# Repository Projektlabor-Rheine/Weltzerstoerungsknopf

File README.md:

# Weltzerstoerungsknopf
The Repo of Earth destruction :D

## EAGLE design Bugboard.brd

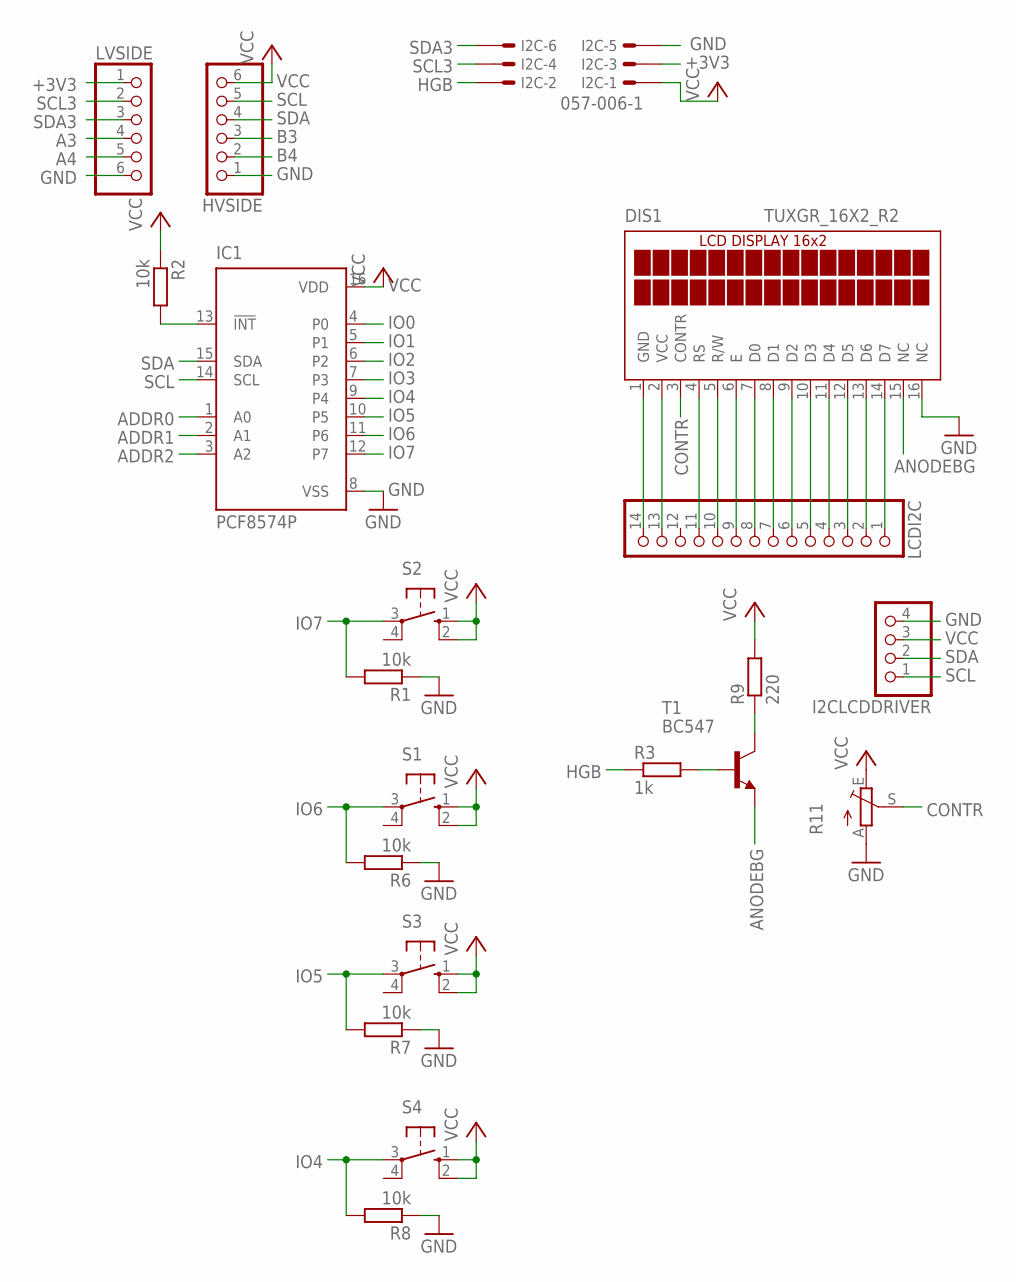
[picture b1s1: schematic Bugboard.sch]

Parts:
DIS1: TUXGR_16X2_R2
HVSIDE: PINHD-1X6; 1X06
I2C: 057-006-1
I2CLCDDRIVER: PINHD-1X4; 1X04
IC1: PCF8574P; DIL16
LCDI2C: PINHD-1X14; 1X14
LVSIDE: PINHD-1X6; 1X06
R1, R2, R6, R7, R8: 10k; 0204/7
R3: 1k; 0207/12
R9: 220; 0204/7
R11: TRIM_EU-B64Y; B64Y
S1, S2, S3, S4: 10-XX; B3F-10XX
T1: BC547; TO92

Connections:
+3V3: I2C.3, LVSIDE.1
A3: LVSIDE.4
A4: LVSIDE.5
ADDR0: IC1.1 (A0)
ADDR1: IC1.2 (A1)
ADDR2: IC1.3 (A2)
ANODEBG: DIS1.15 (NC), T1.1 (E)
B3: HVSIDE.3
B4: HVSIDE.2
CONTR: DIS1.3 (CONTR), R11.S
GND: DIS1.1 (GND), DIS1.16 (NC), HVSIDE.1, I2C.5, I2CLCDDRIVER.4, IC1.8 (VSS), LCDI2C.14, LVSIDE.6, R1.1, R6.1, R7.1, R8.1, R11.A
HGB: I2C.2, R3.1
IO0: IC1.4 (P0)
IO1: IC1.5 (P1)
IO2: IC1.6 (P2)
IO3: IC1.7 (P3)
IO4: IC1.9 (P4), R8.2, S4.3
IO5: IC1.10 (P5), R7.2, S3.3
IO6: IC1.11 (P6), R6.2, S1.3
IO7: IC1.12 (P7), R1.2, S2.3
unnamed: IC1.13 (!INT), R2.2
unnamed: DIS1.14 (D7), LCDI2C.1
unnamed: DIS1.13 (D6), LCDI2C.2
unnamed: DIS1.12 (D5), LCDI2C.3
unnamed: DIS1.11 (D4), LCDI2C.4
unnamed: DIS1.10 (D3), LCDI2C.5
unnamed: DIS1.9 (D2), LCDI2C.6
unnamed: DIS1.8 (D1), LCDI2C.7
unnamed: DIS1.7 (D0), LCDI2C.8
unnamed: DIS1.6 (E), LCDI2C.9
unnamed: DIS1.5 (R/W), LCDI2C.10
unnamed: DIS1.4 (RS), LCDI2C.11
unnamed: R9.1, T1.3 (C)
unnamed: R3.2, T1.2 (B)
SCL: HVSIDE.5, I2CLCDDRIVER.1, IC1.14 (SCL)
SCL3: I2C.4, LVSIDE.2
SDA: HVSIDE.4, I2CLCDDRIVER.2, IC1.15 (SDA)
SDA3: I2C.6, LVSIDE.3
VCC: DIS1.2 (VCC), HVSIDE.6, I2C.1, I2CLCDDRIVER.3, IC1.16 (VDD), LCDI2C.13, R2.1, R9.2, R11.E, S1.1 (S), S1.2 (S1), S2.1 (S), S2.2 (S1), S3.1 (S), S3.2 (S1), S4.1 (S), S4.2 (S1)

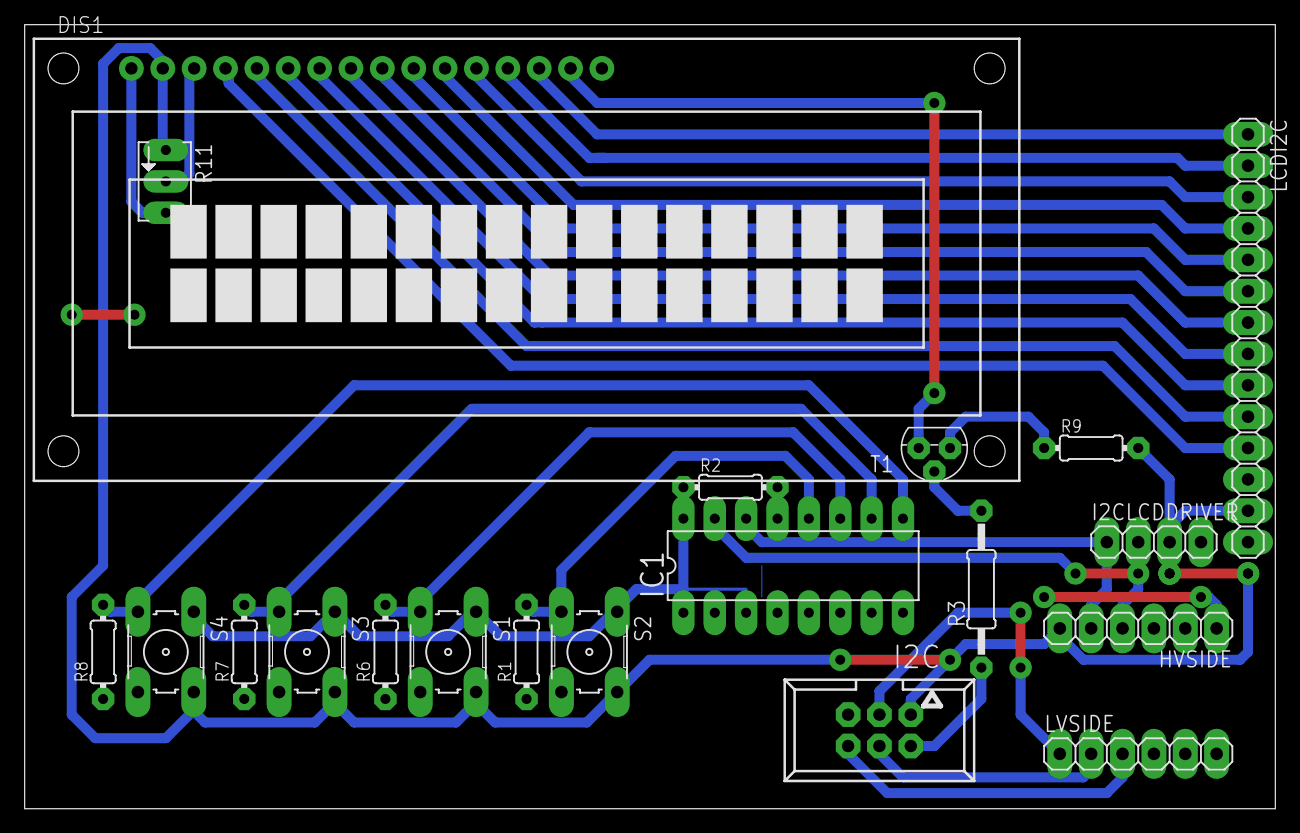
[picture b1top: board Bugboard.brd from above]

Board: 2 copper layers, 101.3 x 63.5 mm, 20 parts (0 on the bottom side), 28 nets.

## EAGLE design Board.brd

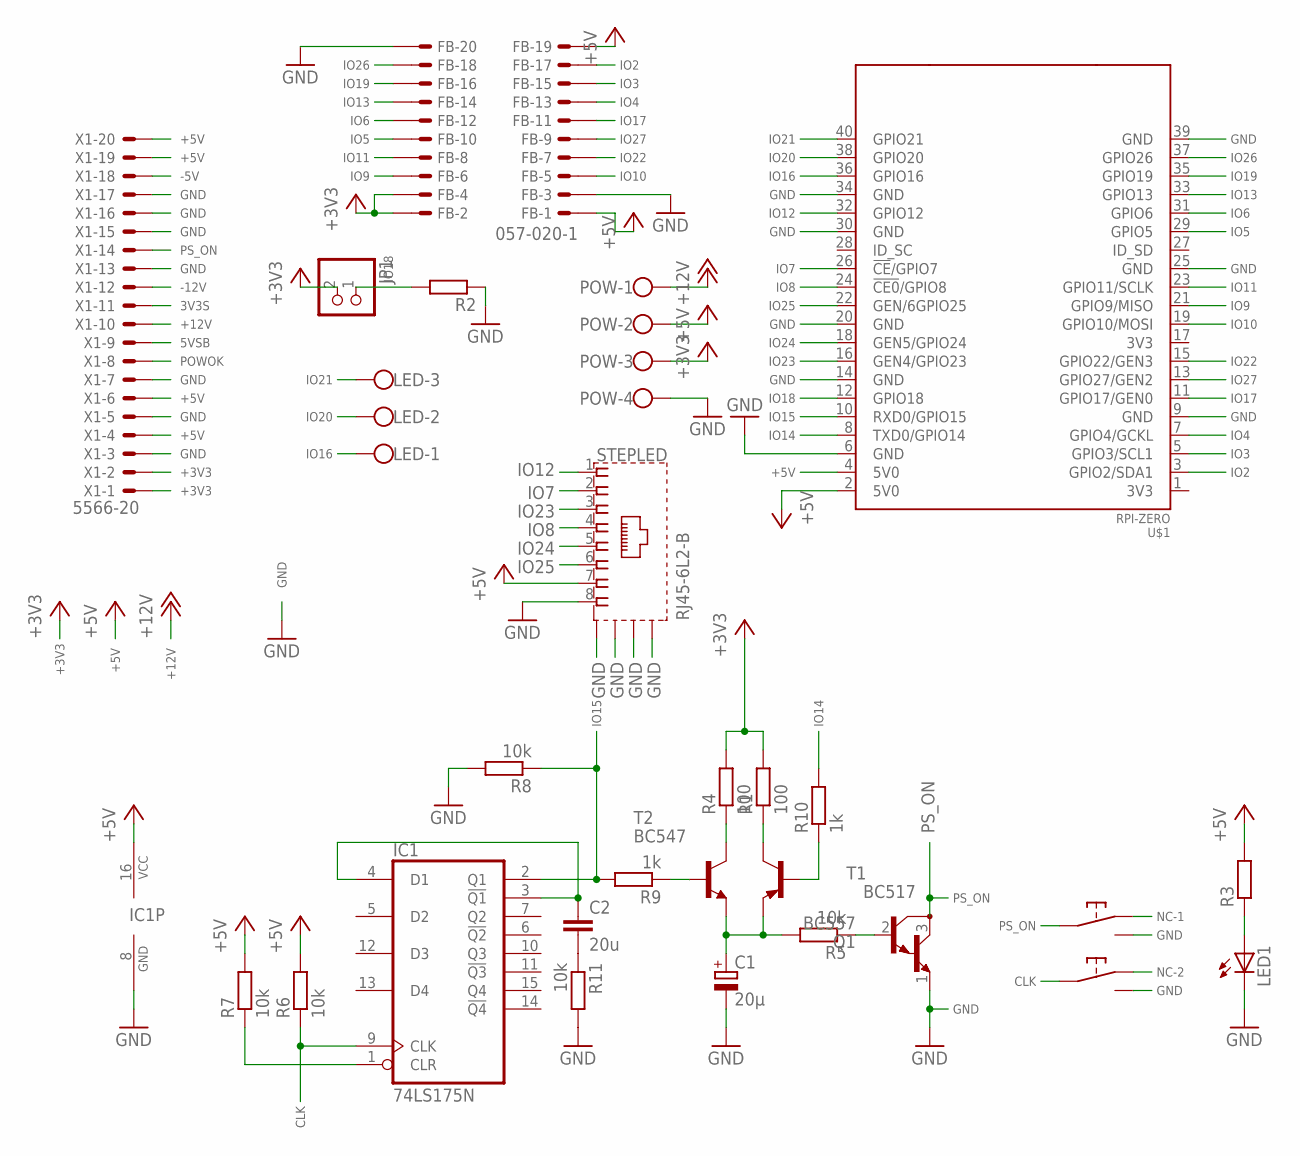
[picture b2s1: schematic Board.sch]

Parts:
C1: 20µ; E2,5-6E
C2: 20u; C050-024X044
FB: 057-020-1
IC1: 74LS175N; DIL16
JP1: PINHD-1X2; 1X02
LED: W237-103
LED1: LED3MM
POW: W237-4
Q1: BC557; TO92
R1, R4: 100; 0204/7
R2: R-EU_0204/7; 0204/7
R3: R-EU_0204/5; 0204/5
R5, R6, R7, R8, R11: 10k; 0204/7
R9, R10: 1k; 0204/7
STEPLED: RJ45-6L2-B; RJ45-SHIELD2
T1: BC517; TO92
T2: BC547; TO92
U$1: RPI-ZERO; RASPBERRYPI_BASTELSTUBE_V13_RASPI_BOARD_B+_FULL
U$2: PC-SWITCH
X1: 5566-20

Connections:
3V3S: X1.11
5VSB: X1.9
+3V3: FB.2, FB.4, JP1.2, POW.3, R1.2, R4.2, X1.1, X1.2
+5V: FB.1, FB.19, IC1.16 (VCC), POW.2, R3.2, R6.2, R7.2, STEPLED.7, U$1.2 (5V0), U$1.4 (5V0), X1.4, X1.6, X1.19, X1.20
+12V: POW.1, X1.10
-5V: X1.18
-12V: X1.12
CLK: IC1.9 (CLK), R6.1, U$2.COM$5
CLR: IC1.1 (CLR), R7.1
GND: C1.-, FB.3, FB.20, IC1.8 (GND), LED1.K (C), POW.4, R2.1, R8.2, R11.2, STEPLED.8, STEPLED.S1 (S), STEPLED.S2 (S), STEPLED.S3 (S), STEPLED.S4 (S), T1.1 (E), U$1.6 (GND), U$1.9 (GND), U$1.14 (GND), U$1.20 (GND), U$1.25 (GND), U$1.30 (GND), U$1.34 (GND), U$1.39 (GND), U$2.NO$3, U$2.NO$6, X1.3, X1.5, X1.7, X1.13, X1.15, X1.16, X1.17
IO2: FB.17, U$1.3 (GPIO2/SDA1)
IO3: FB.15, U$1.5 (GPIO3/SCL1)
IO4: FB.13, U$1.7 (GPIO4/GCKL)
IO5: FB.10, U$1.29 (GPIO5)
IO6: FB.12, U$1.31 (GPIO6)
IO7: STEPLED.2, U$1.26 (!CE!/GPIO7)
IO8: STEPLED.4, U$1.24 (!CE0!/GPIO8)
IO9: FB.6, U$1.21 (GPIO9/MISO)
IO10: FB.5, U$1.19 (GPIO10/MOSI)
IO11: FB.8, U$1.23 (GPIO11/SCLK)
IO12: STEPLED.1, U$1.32 (GPIO12)
IO13: FB.14, U$1.33 (GPIO13)
IO14: R10.2, U$1.8 (TXD0/GPIO14)
IO15: IC1.2 (Q1), R8.1, R9.2, U$1.10 (RXD0/GPIO15)
IO16: LED.1, U$1.36 (GPIO16)
IO17: FB.11, U$1.11 (GPIO17/GEN0)
IO18: JP1.1, R2.2, U$1.12 (GPIO18)
IO19: FB.16, U$1.35 (GPIO19)
IO20: LED.2, U$1.38 (GPIO20)
IO21: LED.3, U$1.40 (GPIO21)
IO22: FB.7, U$1.15 (GPIO22/GEN3)
IO23: STEPLED.3, U$1.16 (GEN4/GPIO23)
IO24: STEPLED.5, U$1.18 (GEN5/GPIO24)
IO25: STEPLED.6, U$1.22 (GEN/6GPIO25)
IO26: FB.18, U$1.37 (GPIO26)
IO27: FB.9, U$1.13 (GPIO27/GEN2)
unnamed: C2.2, R11.1
unnamed: R4.1, T2.3 (C)
unnamed: Q1.3 (C), R1.1
unnamed: Q1.2 (B), R10.1
unnamed: LED1.A, R3.1
unnamed: C2.1, IC1.3 (!Q1), IC1.4 (D1)
unnamed: R9.1, T2.2 (B)
unnamed: R5.1, T1.2 (B)
unnamed: C1.+, Q1.1 (E), R5.2, T2.1 (E)
NC-1: U$2.NC$1
NC-2: U$2.NC$4
POWOK: X1.8
PS_ON: T1.3 (C), U$2.COM$2, X1.14

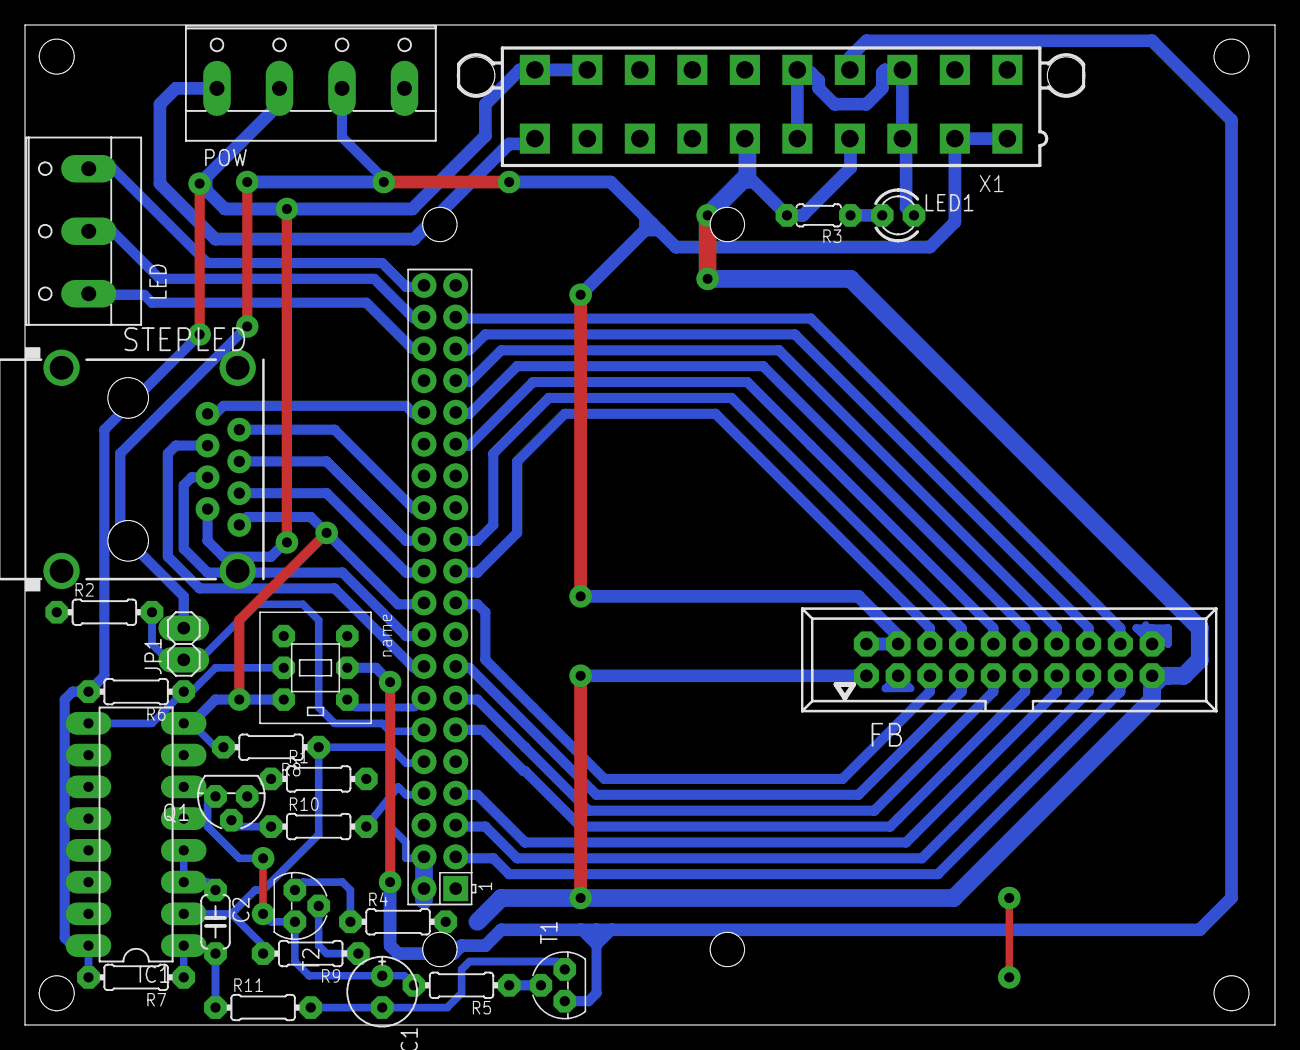
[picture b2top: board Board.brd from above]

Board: 2 copper layers, 100.0 x 80.0 mm, 26 parts (0 on the bottom side), 42 nets.

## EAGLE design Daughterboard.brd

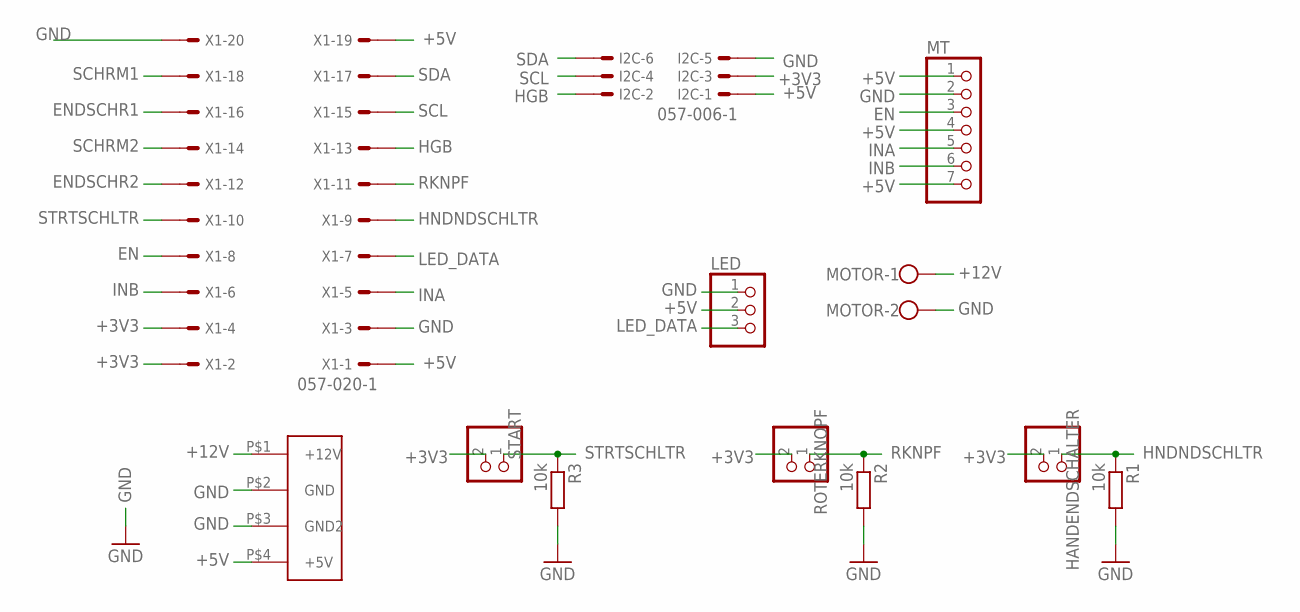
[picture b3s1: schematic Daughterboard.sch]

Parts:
HANDENDSCHALTER: PINHD-1X2; 1X02
I2C: 057-006-1
LED: PINHD-1X3; 1X03
MOTOR: W237-102
MT: PINHD-1X7; 1X07
R1, R2, R3: 10k; 0204/7
ROTERKNOPF: PINHD-1X2; 1X02
START: PINHD-1X2; 1X02
U$1: MOLEX_STECKER; MOLEXCONNECTOR
X1: 057-020-1

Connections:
+3V3: HANDENDSCHALTER.2, I2C.3, ROTERKNOPF.2, START.2, X1.2, X1.4
+5V: I2C.1, LED.2, MT.1, MT.4, MT.7, U$1.P$4 (+5V), X1.1, X1.19
+12V: MOTOR.1, U$1.P$1 (+12V)
EN: MT.3, X1.8
ENDSCHR1: X1.16
ENDSCHR2: X1.12
GND: I2C.5, LED.1, MOTOR.2, MT.2, R1.2, R2.2, R3.2, U$1.P$2 (GND), U$1.P$3 (GND2), X1.3, X1.20
HGB: I2C.2, X1.13
HNDNDSCHLTR: HANDENDSCHALTER.1, R1.1, X1.9
INA: MT.5, X1.5
INB: MT.6, X1.6
LED_DATA: LED.3, X1.7
RKNPF: R2.1, ROTERKNOPF.1, X1.11
SCHRM1: X1.18
SCHRM2: X1.14
SCL: I2C.4, X1.15
SDA: I2C.6, X1.17
STRTSCHLTR: R3.1, START.1, X1.10

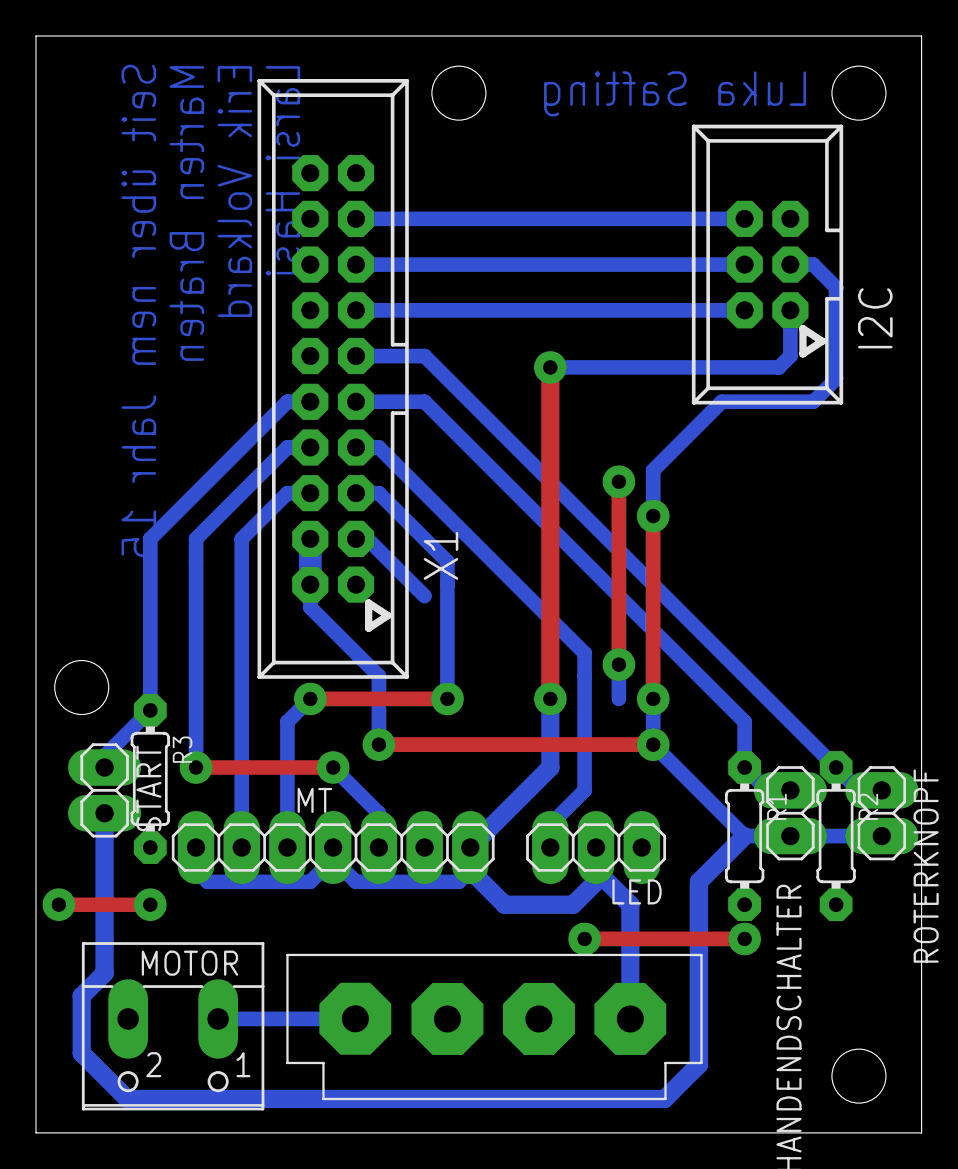
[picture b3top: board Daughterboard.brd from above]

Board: 2 copper layers, 49.2 x 60.9 mm, 12 parts (0 on the bottom side), 14 nets.

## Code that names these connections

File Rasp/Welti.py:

#!/usr/bin/python


#DDDASSSS Selbstzerstörungsskript

import RPi.GPIO as GPIO
import time
import os.path
import os
import asyncio
from functools import partial
from escpos.printer import Usb
import random


#CONST
#Shutdown
#IO14 is already handled
SHTDWN = 15
#schere
SCHM1 = 26
SCHM2 = 13
SCHE1 = 19
SCHE2 = 6
#I2C
SDAP = 2
SCLP = 3
HGB = 4
#Perry
RTKNPF = 17
HNDNDSCHLTR = 27
RTSCHLTR = 5
NEBEL = 16
#Hand
EN = 11
INA = 10
INB = 9
#LED
LEDR = 22
LEDS1 = 21
LEDS2 = 20
#LED Schritte
WLTSCHRFT = 12
STEP1 = 23
STEP2 = 8
STEP3 = 25
#Movement
FORWARD, BACKWARD, STOP = range(0,3)
#Steps
SCHTZKPPSCHLTR, RTNKNPFDRCKN, QUTTNGNTNHMN, OFF = range(4,8)
#otherstuff
counterfile = "/home/pi/Welti/counter.txt"
CRCL = "\n"


#Vars
cntr = 0


#GPIO setup
GPIO.setmode(GPIO.BCM)
GPIO.setwarnings(False)

#Scheren pins
GPIO.setup([SCHM1, SCHM2, NEBEL], GPIO.OUT, initial=GPIO.LOW)
GPIO.setup([SCHE1, SCHE2], GPIO.IN)
#Perry
GPIO.setup([RTKNPF, HNDNDSCHLTR, RTSCHLTR], GPIO.IN)
#Hand
GPIO.setup([EN, INA, INB], GPIO.OUT, initial=GPIO.LOW)
#LED schrift
GPIO.setup([WLTSCHRFT, STEP1, STEP2, STEP3], GPIO.OUT, initial=GPIO.HIGH)
#Shutdown
GPIO.setup(SHTDWN, GPIO.IN)

#Event detect
GPIO.add_event_detect(SHTDWN, GPIO.FALLING)

#Printer setupo
p = Usb(0x0416, 0x5011)

#Startup IO
if not(os.path.isfile(counterfile)):
    fl = open(counterfile, "w")
    fl.write("0" + CRCL)
    fl.close()

cntrfl = open(counterfile, "r")
cntr = int(cntrfl.readline())
cntrfl.close()



def shutdown(channel):
    time.sleep(0.2)
    if GPIO.input(channel) == 0:
        os.system("shutdown -t 1")
        quit()

def back_to_idle_in(channel, task):
    time.sleep(1)
    if GPIO.input(channel) == 1:
        print("back to idle trigerred")
        print(task)
        task.cancel()
        GPIO.remove_event_detect(RTKNPF)

def schere(action):
    print("schere")
    if action == FORWARD:
        print("juergen")
        GPIO.output(SCHM1, GPIO.HIGH)
        GPIO.output(SCHM2, GPIO.LOW)
    elif action == BACKWARD:
        print("joachim")
        GPIO.output(SCHM1, GPIO.LOW)
        GPIO.output(SCHM2, GPIO.HIGH)
    else:
        print("waldemar")
        GPIO.output(SCHM1, GPIO.LOW)
        GPIO.output(SCHM2, GPIO.LOW)

def hand(action):
    if action == FORWARD:
        GPIO.output(EN, GPIO.HIGH)
        GPIO.output(INA, GPIO.LOW)
        GPIO.output(INB, GPIO.HIGH)
    elif action == BACKWARD:
        GPIO.output(EN, GPIO.HIGH)
        GPIO.output(INA, GPIO.HIGH)
        GPIO.output(INB, GPIO.LOW)
    else:
        GPIO.output(EN, GPIO.LOW)
        GPIO.output(INA, GPIO.LOW)
        GPIO.output(INB, GPIO.LOW)

def save_cntr(cntr):
    cntrfl = open(counterfile, 'w')
    cntrfl.write(str(cntr) + CRCL)
    cntrfl.close()

def led_step(step):
    if step == SCHTZKPPSCHLTR:
        GPIO.output(STEP1, GPIO.LOW)
        GPIO.output(STEP2, GPIO.HIGH)
        GPIO.output(STEP3, GPIO.HIGH)
    elif step == RTNKNPFDRCKN:
        GPIO.output(STEP1, GPIO.HIGH)
        GPIO.output(STEP2, GPIO.LOW)
        GPIO.output(STEP3, GPIO.HIGH)
    elif step == QUTTNGNTNHMN:
        GPIO.output(STEP1, GPIO.HIGH)
        GPIO.output(STEP2, GPIO.HIGH)
        GPIO.output(STEP3, GPIO.LOW)
    else:
        GPIO.output(STEP1, GPIO.HIGH)
        GPIO.output(STEP2, GPIO.HIGH)
        GPIO.output(STEP3, GPIO.HIGH)

async def print_qui(cntr):
    #Print und so
    print("Druckauftrag: " + str(cntr))
    p.text(" Sie sind der " + str(cntr) + ". der seit Anfang der MAKER FAIRE HANNOVER 2019 \n die Welt zerstoeren wollte!")
    p.text("\n")
    ran = random.randint(1, 101)
    if cntr == 666:
        p.image("/home/pi/Welti/Bernsen.png")
        p.text("Muhahahahaha")
    else:
        p.image("/home/pi/Welti/Pilzi.png")
    if ran == 42:
        p.image("/home/pi/Welti/Afting.jpeg")
        p.text("Herzlichen Glueckwunsch, sie haben einen Glücks-Afting bekommen. Kommen sie zum Projektlabor-stand und lösen sie diese Quittung gegen ein kleines Geschenk ein")
    p.text("\n")
    p.cut()
    #warten und so
    #await asyncio.sleep(1) 
    print("print und so")
    schere(FORWARD)
    GPIO.wait_for_edge(SCHE2, GPIO.RISING)
    schere(BACKWARD)
    GPIO.wait_for_edge(SCHE1, GPIO.RISING)
    schere(STOP)

async def idle():
    #LED Streifen und Ring fehlt
    while True:
        GPIO.output(WLTSCHRFT, GPIO.LOW)
        await asyncio.sleep(5)
        GPIO.output(WLTSCHRFT, GPIO.HIGH)
        await asyncio.sleep(0.2)

async def rtknpf():
    print("rtknpf task is running")
    GPIO.add_event_detect(RTKNPF, GPIO.FALLING)
    while True:
        if GPIO.event_detected(RTKNPF):
            pass
        await asyncio.sleep(0.5)
        if GPIO.input(RTKNPF) == 0:
            GPIO.remove_event_detect(RTKNPF)
            return

async def nebelshuht(cntr):
    GPIO.output(NEBEL, GPIO.HIGH)
    if cntr == 666:
        await asyncio.sleep(5)
    else:
        await asyncio.sleep(0.25)
    GPIO.output(NEBEL, GPIO.LOW)
    await asyncio.sleep(0.05)

#Mainloop
async def main(cntr):
    
    while True: 
        print("inside main loop")
        #LED Streifen und Ring fehlt
        led_step(STEP1)
        
        idletask = asyncio.create_task(idle())
        print("idletask started")
        GPIO.remove_event_detect(RTSCHLTR)
        GPIO.wait_for_edge(RTSCHLTR, GPIO.FALLING)
        GPIO.remove_event_detect(RTSCHLTR)
        #Roter Schalter umgelegt
        idletask.cancel()
        GPIO.output(WLTSCHRFT, GPIO.LOW)
        
        #Schritt 2
        #LED Streifen und Ring fehlt
        led_step(STEP2)
        #iwie task übergebn
        rtknpftask = asyncio.create_task(rtknpf())
        GPIO.add_event_detect(RTSCHLTR, GPIO.RISING, callback=partial(back_to_idle_in, task=rtknpftask))
        print("task created")
        try:
            print("awaiting...")
            await rtknpftask
            print("awaited")
        except asyncio.CancelledError:
            print("continued")
            continue
        led_step(OFF)
        cntr += 1
        GPIO.remove_event_detect(RTSCHLTR)
        #Schritt 3
        hand(FORWARD)
        nebeltask = asyncio.create_task(nebelshuht(cntr))
        print("hand forward")
        #LED Streifen und Ring fehlt
        while True:
            GPIO.wait_for_edge(RTSCHLTR, GPIO.RISING)
            await asyncio.sleep(0.5)
            if GPIO.input(RTSCHLTR) == 1:
                break
        GPIO.remove_event_detect(RTSCHLTR)
        hand(BACKWARD)
        #LED Streifen und Ring fehlt
        led_step(STEP3)
        printtask = asyncio.create_task(print_qui(cntr))
        while True:
            GPIO.wait_for_edge(HNDNDSCHLTR, GPIO.FALLING)
            await asyncio.sleep(0.5)
            if GPIO.input(HNDNDSCHLTR) == 0:
                break
        hand(STOP)
        await asyncio.sleep(1)
        print("handstopped")
        save_cntr(cntr)

        await printtask



#Startup
print("startup")
if GPIO.input(SCHE1) == 0:
    schere(BACKWARD)
    GPIO.wait_for_edge(SCHE1, GPIO.RISING)
    schere(STOP)

print("schere ok")

if GPIO.input(HNDNDSCHLTR) == 1:
    hand(BACKWARD)
    GPIO.wait_for_edge(HNDNDSCHLTR, GPIO.FALLING)
    hand(STOP)

print("hand ok")

#Add event callbacks
GPIO.add_event_callback(SHTDWN, shutdown)

print("before main loop")

#Mainloop
asyncio.run(main(cntr))

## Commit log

2019-09-15 First commit wuhu
2019-09-15 running version no cool
2019-09-15 Bugboard and i2clcd
2019-09-15 moved terminal.py
2019-09-16 json interpretation
2019-09-16 vlt working advanced display and YesNoMenu
2019-09-19 Added Scrolllist
2019-09-29 first i2c button input test
2019-10-03 Added InObj and ViewObj
2019-10-03 Implementation of InObj to YNMenu
2019-10-03 fixed button read bugs and added Edges
2019-10-03 added Label in YNMenu and ScrollList OK detection
2019-10-03 removed some issues and restructured terminal.py
2019-10-03 maybe working 1st terminal
2019-10-05 added TextList
2019-10-05 halfway runnable
2019-10-05 counting of lines starts with 0
2019-10-05 first running test version
2019-10-05 Almost working ynmenu
2019-10-05 runnable version with YNMenu
